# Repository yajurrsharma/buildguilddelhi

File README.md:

# Build Guild Delhi
Made during Build Guild Delhi

# SCHEMATIC

I've used a 3x4 Key Matrix, along with an SSD1306 OLED Screen, and a Rotary Encoder

## PCB

## 3D Model

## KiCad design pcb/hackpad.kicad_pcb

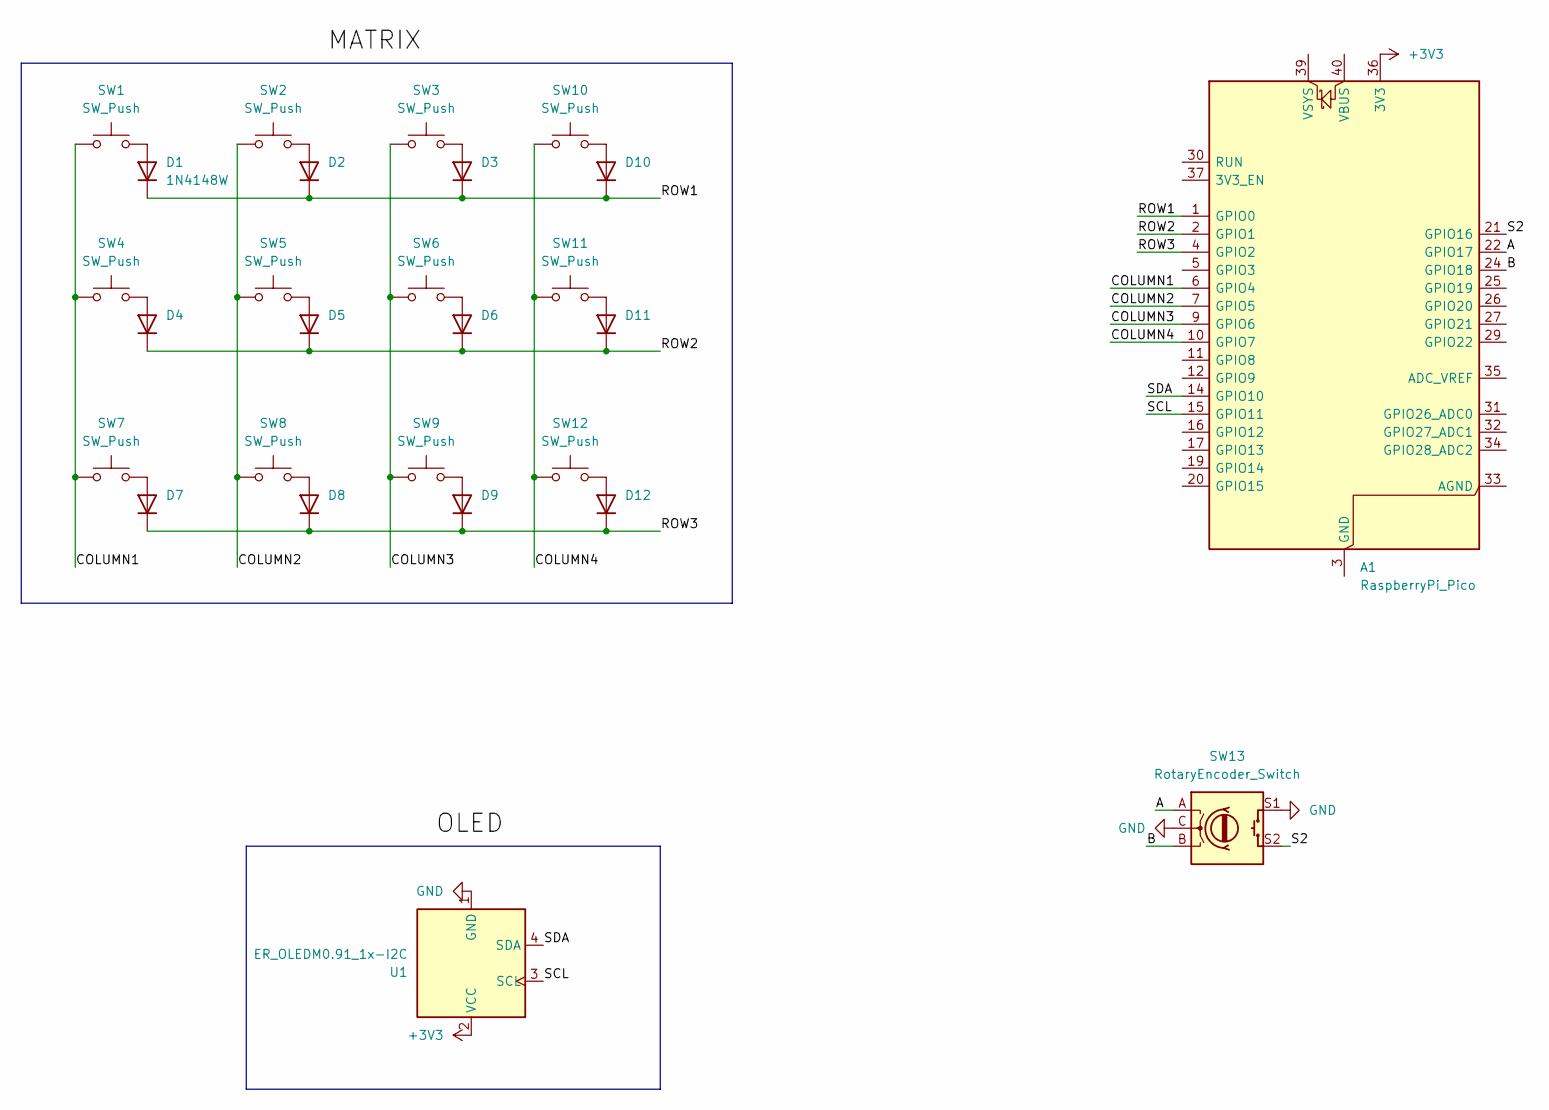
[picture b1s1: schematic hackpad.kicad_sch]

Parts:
A1: RaspberryPi_Pico; RaspberryPi_Pico_Common_Unspecified
D1, D2, D3, D4, D5, D6, D7, D8, D9, D10, D11, D12: 1N4148W; D_SOD-123
SW1, SW2, SW3, SW4, SW5, SW6, SW7, SW8, SW9, SW10, SW11, SW12: SW_Push; SW_Cherry_MX_1.00u_PCB
SW13: RotaryEncoder_Switch; RotaryEncoder_Alps_EC11E-Switch_Vertical_H20mm
U1: ER_OLEDM0.91_1x-I2C

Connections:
+3V3: A1.36 (3V3), U1.2 (VCC)
/A: A1.22 (GPIO17), SW13.A
/B: A1.24 (GPIO18), SW13.B
/COLUMN1: A1.6 (GPIO4), SW1.1, SW4.1, SW7.1
/COLUMN2: A1.7 (GPIO5), SW2.1, SW5.1, SW8.1
/COLUMN3: A1.9 (GPIO6), SW3.1, SW6.1, SW9.1
/COLUMN4: A1.10 (GPIO7), SW10.1, SW11.1, SW12.1
/ROW1: A1.1 (GPIO0), D1.1 (K), D2.1 (K), D3.1 (K), D10.1 (K)
/ROW2: A1.2 (GPIO1), D4.1 (K), D5.1 (K), D6.1 (K), D11.1 (K)
/ROW3: A1.4 (GPIO2), D7.1 (K), D8.1 (K), D9.1 (K), D12.1 (K)
/S2: A1.21 (GPIO16), SW13.S2
/SCL: A1.15 (GPIO11), U1.3 (SCL)
/SDA: A1.14 (GPIO10), U1.4 (SDA)
GND: SW13.C, SW13.S1, U1.1 (GND)
unnamed: A1.3 (GND), A1.8 (GND), A1.13 (GND), A1.18 (GND), A1.23 (GND), A1.28 (GND), A1.38 (GND)
unnamed: D1.2 (A), SW1.2
unnamed: D2.2 (A), SW2.2
unnamed: D3.2 (A), SW3.2
unnamed: D4.2 (A), SW4.2
unnamed: D5.2 (A), SW5.2
unnamed: D6.2 (A), SW6.2
unnamed: D7.2 (A), SW7.2
unnamed: D8.2 (A), SW8.2
unnamed: D9.2 (A), SW9.2
unnamed: D10.2 (A), SW10.2
unnamed: D11.2 (A), SW11.2
unnamed: D12.2 (A), SW12.2

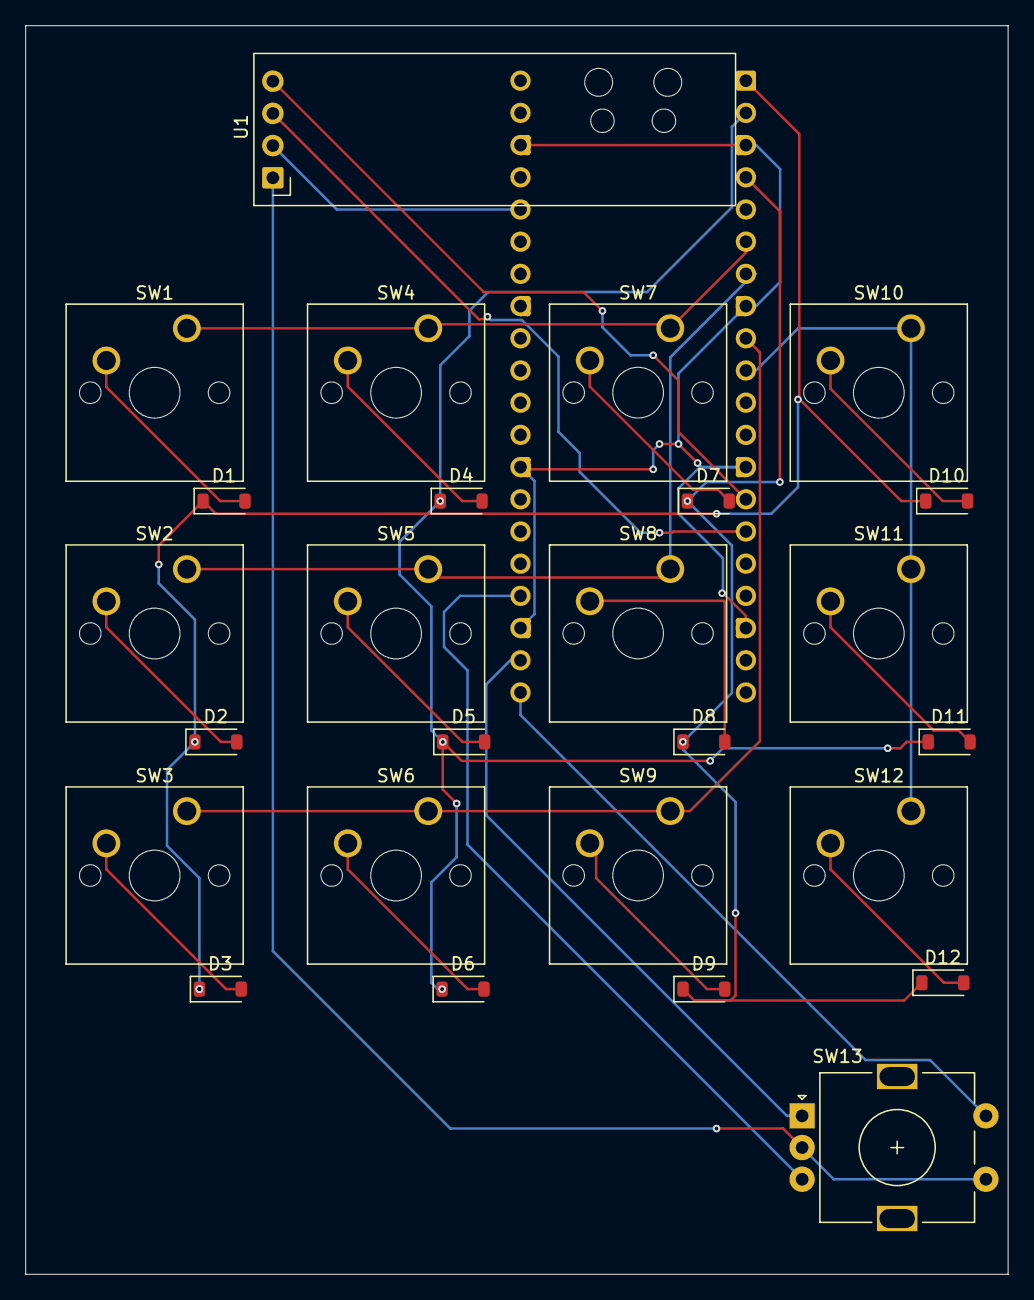
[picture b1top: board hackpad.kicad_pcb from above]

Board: 2 copper layers, 77.5 x 98.5 mm, 27 parts (1 on the bottom side), 27 nets.
